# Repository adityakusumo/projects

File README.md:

# FPGA & Embedded Systems Portfolio

Welcome to my portfolio of FPGA and Embedded Systems projects. This repository showcases various hardware designs (KiCad), SoC implementations (LiteX), and firmware development (C/RISC-V) across different FPGA platforms.

## 🚀 Projects Overview

| Project | Platform | Key Features |
| :--- | :--- | :--- |
| **[01. LCD 10.4" Tester](./01_LCD_Tester_Spartan6)** | Spartan-6 (XC6SLX25) | LVDS high-res portrait display tester, Custom Firmware (ISE/LiteX). |
| **[02. STCC1 Record Module](./02_STCC1_Spartan6_Module)** | Spartan-6 (XC6SLX25) | Custom PCB Design (KiCad), LiteX SoC Integration, DDR3 Memory. |
| **[03. Z-Turn Board SoC](./03_ZTurn_XC7Z020_SoC)** | Zynq-7000 (XC7Z020) | LiteX SoC on MYIR Z-Turn, Temperature Sensing, LVDS support. |
| **[04. Wukong Board SoC](./04_Wukong_XC7A100T_SoC)** | Artix-7 (XC7A100T) | LiteX SoC on Qmtech Wukong, HDMI output, RISC-V (SERV/VexRiscv). |

---

## 🛠 Technologies & Tools

- **Languages:** Verilog, Python (Migen/LiteX), C (Embedded), Bash
- **SoC Framework:** [LiteX](https://github.com/enjoy-digital/litex) (Migen-based SoC builder)
- **EDA Tools:** KiCad (PCB), Xilinx ISE 14.7, Xilinx Vivado
- **Hardware Debugging:** openFPGALoader, litex_term, JTAG, Oscilloscope

---

## 📂 Repository Structure

```text
.
├── 01_LCD_Tester_Spartan6/    # LCD portrait display tester project
├── 02_STCC1_Spartan6_Module/  # Custom Record Module (Hardware + Firmware)
├── 03_ZTurn_XC7Z020_SoC/      # LiteX SoC on Zynq-7000 Platform
└── 04_Wukong_XC7A100T_SoC/    # LiteX SoC on Artix-7 Platform
```

Each directory contains its own documentation and build instructions.

---
*Created and maintained by [Aditya Kusumo](https://github.com/adityakusumo)*

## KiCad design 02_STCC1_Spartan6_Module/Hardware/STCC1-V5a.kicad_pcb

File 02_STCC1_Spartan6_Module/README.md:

# STCC1 Spartan-6 Record Module

This project consists of a custom-designed PCB and a LiteX-based SoC for a data recording module using the Xilinx Spartan-6 FPGA.

## 📂 Project Components

- **[Hardware](./Hardware):** KiCad PCB design files for the STCC1-V5a Record Module. Includes schematics, PCB layout, and production files.
- **[Firmware](./Firmware):** LiteX SoC implementations, including DDR3 support and integration with Xilinx ISE.

## 🛠 Features

- **FPGA:** Spartan-6 XC6SLX25-FTG256.
- **Memory:** DDR3 RAM integration via LiteX.
- **Tools:** KiCad for PCB, LiteX for SoC generation, Xilinx ISE for gateware.

---

## 🚀 Quick Start (Firmware)

1. Navigate to `Firmware/stcc1_xc6slx25/`.
2. Run `./build_firmware.sh b` to build the SoC.
3. Run `./build_firmware.sh m` to compile the RISC-V firmware.
4. Load the bitstream using `openFPGALoader`.

For detailed hardware build instructions, refer to the `Hardware` directory.

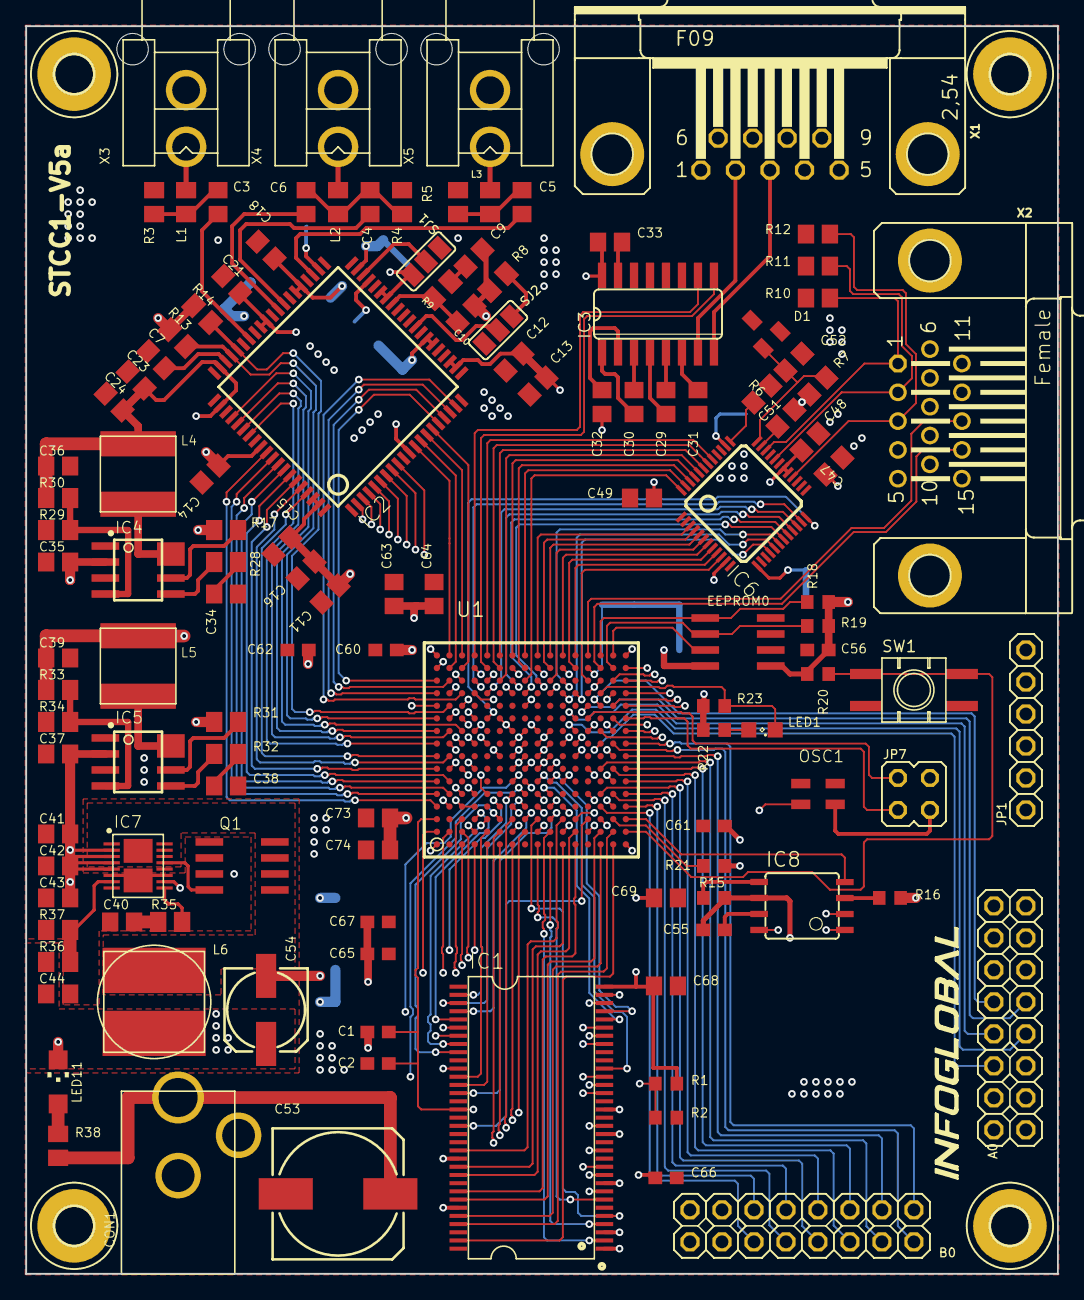
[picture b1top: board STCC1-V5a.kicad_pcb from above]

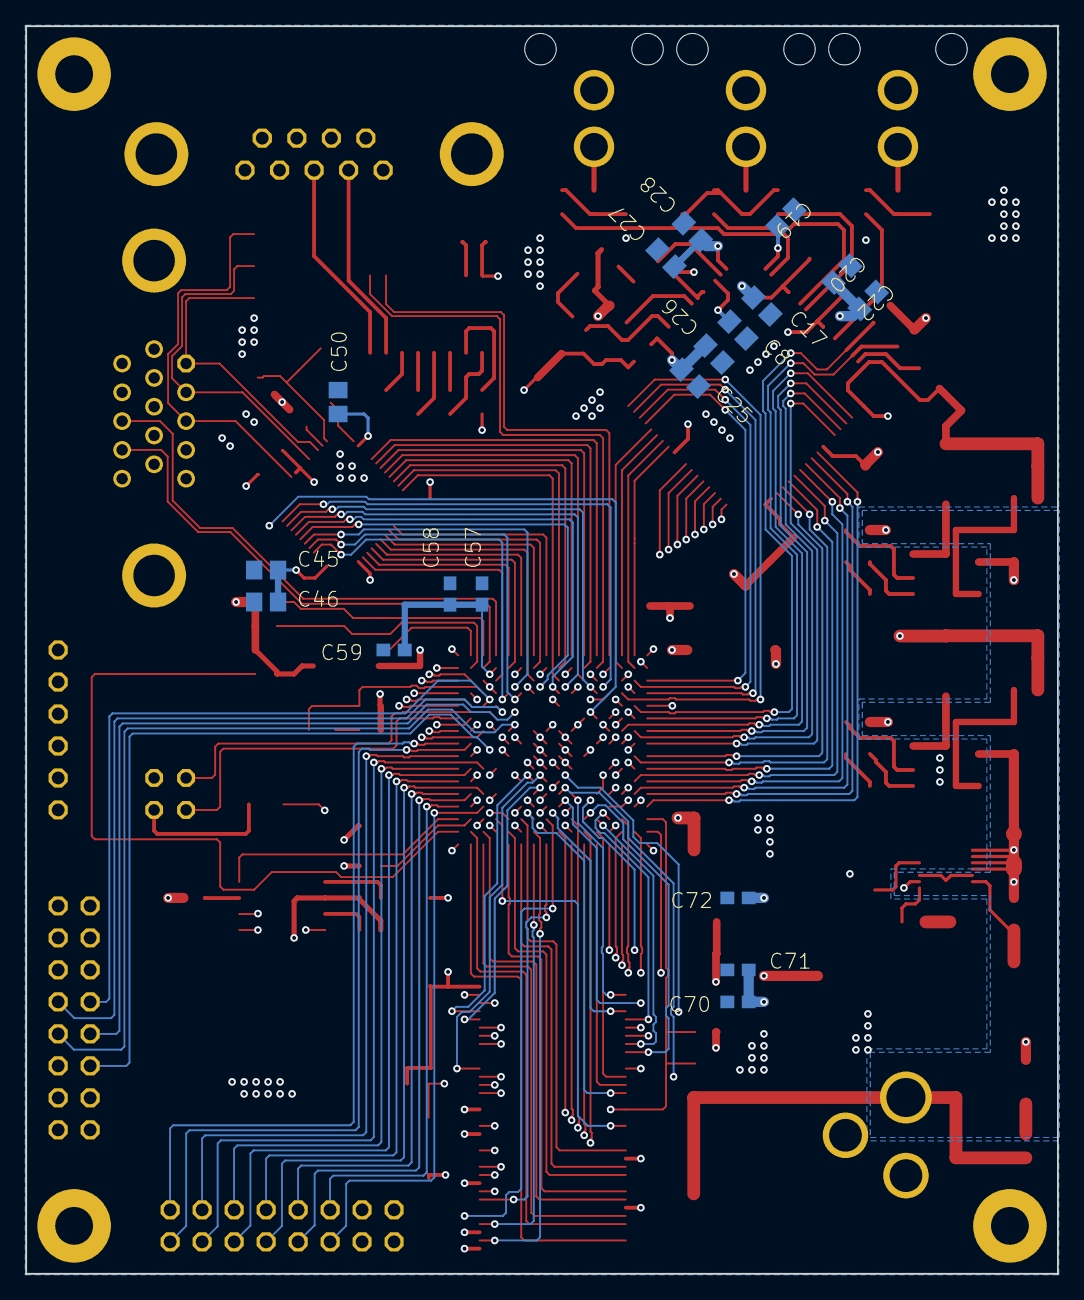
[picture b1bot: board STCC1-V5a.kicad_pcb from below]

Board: 4 copper layers, 81.9 x 99.1 mm, 147 parts (18 on the bottom side), 197 nets.

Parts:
A0: 2X08
B0: 2X08
C1, C2, C57, C58, C59, C60, C61, C62, C65, C66, C67, C70, C71, C72: 4u7; C0603
C3, C4, C5: 47n; C0805
C6: 1n; C0805
C7, C8, C11, C12, C13, C14, C15, C16, C17, C18, C19, C20, C21, C22, C23, C24, C25, C26, C27, C28, C29, C30, C31, C32, C33, C45, C46, C47, C51: 100n; C0805
C9: 82n; C0805
C10: 8.2n; C0805
C34, C38, C40: 2n2; C0805
C35, C37, C41, C42, C43: 10u; C0805
C36, C39, C44, C63, C64, C68, C69, C73, C74: 22u; C0805
C48, C49, C50: 10n; C0805
C52: 1u; C0805
C53: 470u,25V; 153CLV-1014
C54: 100u,16V; 153CLV-0605
C55, C56: 100n; C0603
CON1: DC_SOCKET5870; PWR-5870
D1: AD1580; SOT23
EEPROM0: AT24C512-BN; SOIC8
H1, H2, H3, H4: MOUNT-PAD-ROUND3.0; 3,0-PAD
IC1: DDR_SDRAM-512X16TSOPII-66; TSOPII-66
IC2: AD9883A; LQFP80
IC3: MAX3232ESE; SO16
IC4, IC5: AOZ1021
IC6: ADV7125; LQFP48
IC7: AOZ1025; DFN-16+2TP
IC8: AT45DB161D-SU; 8S2
JP1: 1X06
JP7: JP2Q
L1, L2, L3: FR; M0805
L4, L5: 4.7u; NR60
L6: 1.5u; VLP80
LED1: GRN; SML0805
LED11: RED; CHIPLED_1206
OSC1: 50Mhz; ASE
Q1: SO-08
R1, R2: 220; R0603
R3, R4, R5: 75; M0805
R6: 560; R0805
R7: 1k; R0805
R8: 10k; M0805
R9: 2k7; M0805
R10, R11, R12: 75; R0805
R13, R14: 4k7; M0805
R15, R16, R20, R21: 4k7; R0603
R17, R28, R29, R31, R32: 7k5; M0805
R18, R19: 1k2; R0603
R22: 1k; R0603
R23: 330; R0603
R30, R34, R37: 2k4; M0805
R33: 5k4; M0805
R35: 25k; M0805
R36: 1k2; M0805
R38: 4K7; M0805
SJ1, SJ2: SJ_2
SW1: RESET; PB0_SMD
U1: 6SLX25FTG256; FT256
U$7: LOGO_MEDIUM
X1: F09HP
X2: HDF15H
X3, X4, X5: RCA1X

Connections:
+1.2V: C44.1, C54.+, C70.1, C71.1, C72.1, C73.1, C74.1, L6.P$2, R36.2, U1.G7, U1.G9, U1.H8, U1.H10, U1.J7, U1.J9, U1.K8, U1.K10
+2.5V: C1.1, C39.1, C65.1, C66.1, C67.1, C68.1, C69.1, IC1.1, IC1.3, IC1.9, IC1.15, IC1.18, IC1.33, IC1.55, IC1.61, L5.P$1, R1.2, R33.2, U1.D2, U1.E5, U1.F8, U1.F11, U1.G4, U1.G10, U1.H6, U1.J2, U1.J10, U1.K4, U1.L6, U1.L9, U1.N2
+3V3: A0.3, A0.4, B0.3, B0.4, C9.2, C10.2, C11.1, C12.1, C13.1, C14.1, C15.1, C16.1, C17.1, C18.1, C19.1, C20.1, C21.1, C22.1, C23.1, C24.1, C25.1, C26.1, C27.1, C28.1, C32.2, C33.2, C36.1, C45.1, C46.1, C47.1, C48.1, C49.1, C50.1, C51.2, C55.1, C56.2, C57.1, C58.1, C59.1, C60.1, C61.1, C62.1, C63.1, C64.1, EEPROM0.1, EEPROM0.8, IC2.11, IC2.22, IC2.23, IC2.26, IC2.27, IC2.34, IC2.35, IC2.39, IC2.42, IC2.45, IC2.46, IC2.51, IC2.52, IC2.59, IC2.62, IC2.69, IC2.78, IC2.79, IC3.16, IC6.11, IC6.13, IC6.29, IC6.30, IC6.38, IC8.6, JP1.2, JP7.2, L4.P$1, OSC1.4, R7.2, R8.2, R13.2, R14.2, R15.2, R16.2, R18.2, R19.2, R20.2, R21.2, R22.1, R23.2, R29.2, SJ1.3, U1.B4, U1.B9, U1.B13, U1.D7, U1.D10, U1.D15, U1.G13, U1.J15, U1.K13, U1.N7, U1.N10, U1.N15, U1.R4, U1.R8, U1.R13
A0: IC1.29, U1.K5
A1: IC1.30, U1.K6
A2: IC1.31, U1.D1
A3: IC1.32, U1.L4
A4: IC1.35, U1.G5
A5: IC1.36, U1.H4
A6: IC1.37, U1.H3
A7: IC1.38, U1.D3
A8: IC1.39, U1.B2
A9: IC1.40, U1.A2
A10: IC1.28, U1.G6
A11: IC1.41, U1.E3
A12: IC1.42, U1.F3
AN_BLUE_IN: L3.1, X5.2
AN_GREEN_IN: L2.1, X4.2
AN_RED_IN: L1.1, X3.2
BA0: IC1.26, U1.C3
BA1: IC1.27, U1.C2
BLUE: IC6.28, R12.2, X2.3
BLUE<0>: IC2.19, U1.C13
BLUE<1>: IC2.18, U1.A13
BLUE<2>: IC2.17, U1.B14
BLUE<3>: IC2.16, U1.A14
BLUE<4>: IC2.15, U1.C15
BLUE<5>: IC2.14, U1.C16
BLUE<6>: IC2.13, U1.B15
BLUE<7>: IC2.12, U1.B16
CAS#: IC1.22, U1.H5
CLKE: IC1.44, U1.F4
CLKN: IC1.46, U1.E1
CLKP: IC1.45, U1.E2
CLK_50MHZ: OSC1.3, U1.M9
DATACK_OUT: IC2.67, U1.A9
DONE: LED1.C, R23.1, U1.P13
DQ0: IC1.2, U1.K2
DQ1: IC1.4, U1.K1
DQ2: IC1.5, U1.J3
DQ3: IC1.7, U1.J1
DQ4: IC1.8, U1.F2
DQ5: IC1.10, U1.F1
DQ6: IC1.11, U1.G3
DQ7: IC1.13, U1.G1
DQ8: IC1.54, U1.L3
DQ9: IC1.56, U1.L1
DQ10: IC1.57, U1.M2
DQ11: IC1.59, U1.M1
DQ12: IC1.60, U1.P2
DQ13: IC1.62, U1.P1
DQ14: IC1.63, U1.R2
DQ15: IC1.65, U1.R1
EEPROM_SCL: EEPROM0.6, R19.1, U1.R15
EEPROM_SDA: EEPROM0.5, R18.1, U1.P16
EEPROM_WP: EEPROM0.7, U1.R16
FLASH_MISO: IC8.8, U1.P10
FLASH_MOSI: IC8.1, U1.T10
FLASH_SCK: IC8.2, U1.R11
FLASH_SS: IC8.4, U1.T3
GND: A0.1, A0.2, B0.1, B0.2, C2.2, C7.1, C8.1, C11.2, C12.2, C13.2, C14.2, C15.2, C16.2, C17.2, C18.2, C19.2, C20.2, C21.2, C22.2, C23.2, C24.2, C25.2, C26.2, C27.2, C28.2, C31.1, C33.1, C34.2, C35.2, C36.2, C37.2, C38.2, C39.2, C40.2, C41.2, C42.2, C43.2, C44.2, C45.2, C46.2, C47.2, C48.2, C49.2, C50.2, C52.2, C53.-, C54.-, C55.2, C56.1, C57.2, C58.2, C59.2, C60.2, C61.2, C62.2, C63.2, C64.2, C65.2, C66.2, C67.2, C68.2, C69.2, C70.2, C71.2, C72.2, C73.2, C74.2, CON1.3, D1.2, EEPROM0.2, EEPROM0.3, EEPROM0.4, IC1.6, IC1.12, IC1.24, IC1.34, IC1.48, IC1.52, IC1.58, IC1.64, IC1.66, IC2.1, IC2.10, IC2.20, IC2.21, IC2.24, IC2.25, IC2.28, IC2.32, IC2.36, IC2.40, IC2.41, IC2.44, IC2.47, IC2.50, IC2.53, IC2.55, IC2.60, IC2.61, IC2.63, IC2.68, IC2.80, IC3.15, IC4.AGND, IC4.PGND, IC5.AGND, IC5.PGND, IC6.1, IC6.2, IC6.12, IC6.14, IC6.15, IC6.25, IC6.26, IC6.27, IC6.31, IC6.33, IC6.39, IC6.40, IC7.6, IC7.11, IC7.18, IC8.7, JP1.1, JP7.4, LED11.C, OSC1.2, Q1.1, Q1.2, Q1.3, R2.1, R3.1, R4.1, R5.1, R6.2, R10.1, R11.1, R12.1, R30.1, R34.1, R37.1, SJ1.1, SJ2.1, SW1.1, SW1.2, U1.A1, U1.A16, U1.B7, U1.B11, U1.C4, U1.D4, U1.D13, U1.E9, U1.G2, U1.G8, U1.G15, U1.H7, U1.H9, U1.H12, U1.J5, U1.J8, U1.K7, U1.K9, U1.L2, U1.L15, U1.M8, U1.N13, U1.P3, U1.P14, U1.R6, U1.R10, U1.T1, U1.T16, X1.5, X1.G1, X1.G2, X2.5, X2.6, X2.7, X2.8, X2.10, X2.G1, X2.G2, X3.1, X4.1, X5.1
GREEN: IC6.32, R11.2, X2.2
GREEN<0>: IC2.9, U1.A12
GREEN<1>: IC2.8, U1.D11
GREEN<2>: IC2.7, U1.C11
GREEN<3>: IC2.6, U1.D9
GREEN<4>: IC2.5, U1.C9
GREEN<5>: IC2.4, U1.C7
GREEN<6>: IC2.3, U1.D5
GREEN<7>: IC2.2, U1.C5
HSYNC_OUT: IC2.66, U1.B10
H_SYNC: U1.N16, X2.13
I2C_SCL: IC2.56, R14.1, U1.B12
I2C_SDA: IC2.57, R13.1, U1.A11
INIT_B: R21.1, U1.R3
IO_A5: A0.5, U1.N5
IO_A6: A0.6, U1.P9
IO_A7: A0.7, U1.M10
IO_A8: A0.8, U1.M11
IO_A9: A0.9, U1.N12
IO_A10: A0.10, U1.P12
IO_A11: A0.11, U1.T12
IO_A12: A0.12, U1.R12
IO_A13: A0.13, U1.T13
IO_A14: A0.14, U1.T14
IO_A15: A0.15, U1.R14
IO_A16: A0.16, U1.T15
IO_B5: B0.5, U1.P4
IO_B6: B0.6, U1.T4
IO_B7: B0.7, U1.R5
IO_B8: B0.8, U1.T5
IO_B9: B0.9, U1.P5
IO_B10: B0.10, U1.T6
IO_B11: B0.11, U1.R7
IO_B12: B0.12, U1.T7
IO_B13: B0.13, U1.P7
IO_B14: B0.14, U1.T8
IO_B15: B0.15, U1.R9
IO_B16: B0.16, U1.T9
LDM: IC1.20, U1.J4
LDQS: IC1.16, U1.H2
M0: JP7.1, U1.T11
M1: JP7.3, U1.N11
unnamed: IC8.3, R16.1
unnamed: C3.1, L1.2, R3.2
unnamed: C3.2, IC2.54
unnamed: IC2.38, SJ1.2
unnamed: C4.2, IC2.48
unnamed: C5.1, L3.2, R5.2
unnamed: C5.2, IC2.43
unnamed: IC8.5, R15.1
unnamed: C6.2, IC2.49
unnamed: C4.1, C6.1, L2.2, R4.2
unnamed: C10.1, IC2.33, R9.2
unnamed: R8.1, SJ2.3
unnamed: IC2.29, SJ2.2
unnamed: C7.2, IC2.58
unnamed: C8.2, IC2.37
unnamed: C32.1, IC3.2
unnamed: C9.1, R9.1
unnamed: LED1.A, R22.2
unnamed: IC6.37, R6.1
unnamed: C52.1, D1.1, IC6.36, R7.1
unnamed: C31.2, IC3.6
unnamed: C30.2, IC3.1
unnamed: C29.1, IC3.4
unnamed: C30.1, IC3.3
unnamed: C29.2, IC3.5
unnamed: C51.1, IC6.35
unnamed: IC4.EN, R17.1
unnamed: IC4.LX, L4.P$2
unnamed: IC4.COMP, R28.2
unnamed: C34.1, R28.1
unnamed: IC4.FB, R29.1, R30.2
unnamed: IC5.COMP, R32.2
unnamed: C38.1, R32.1
unnamed: IC5.EN, R31.1
unnamed: IC7.1, IC7.14, IC7.15, IC7.16, IC7.17, L6.P$1, Q1.5, Q1.6, Q1.7, Q1.8
unnamed: IC5.LX, L5.P$2
unnamed: IC7.13, Q1.4
unnamed: IC5.FB, R33.1, R34.2
unnamed: IC7.7, R36.1, R37.2
unnamed: IC7.9, R35.2
unnamed: C40.1, R35.1
unnamed: LED11.A, R38.1
PROG_B: R20.1, SW1.3, SW1.4, U1.T2
RAS#: IC1.23, U1.J6
RED: IC6.34, R10.2, X2.1
RED<0>: IC2.77, U1.A8
RED<1>: IC2.76, U1.B8
RED<2>: IC2.75, U1.A7
RED<3>: IC2.74, U1.B6
RED<4>: IC2.73, U1.A6
RED<5>: IC2.72, U1.B5
RED<6>: IC2.71, U1.A5
RED<7>: IC2.70, U1.A4
RXD: IC3.9, U1.E15
SOG_OUT: IC2.65, U1.A10
TCK: JP1.5, U1.C14
TDI: JP1.4, U1.C12
TDO: JP1.3, U1.E14
TMS: JP1.6, U1.A15
TXD: IC3.10, U1.D16
UART_RX: IC3.8, X1.3
UART_TX: IC3.7, X1.2
UDM: IC1.47, U1.K3
UDQS: IC1.51, U1.N3
VGA_BLU0: IC6.16, U1.M13
VGA_BLU1: IC6.17, U1.L13
VGA_BLU2: IC6.18, U1.L14
VGA_BLU3: IC6.19, U1.J14
VGA_BLU4: IC6.20, U1.H13
VGA_BLU5: IC6.21, U1.G14
VGA_BLU6: IC6.22, U1.E13
VGA_BLU7: IC6.23, U1.D14
VGA_CLOCK: IC6.24, U1.E11
VGA_GRN0: IC6.3, U1.J16
VGA_GRN1: IC6.4, U1.K15
VGA_GRN2: IC6.5, U1.K16
VGA_GRN3: IC6.6, U1.K14
VGA_GRN4: IC6.7, U1.L16
VGA_GRN5: IC6.8, U1.M15
VGA_GRN6: IC6.9, U1.M16
VGA_GRN7: IC6.10, U1.N14
VGA_RED0: IC6.41, U1.E16
VGA_RED1: IC6.42, U1.F15
VGA_RED2: IC6.43, U1.F16
VGA_RED3: IC6.44, U1.F14
VGA_RED4: IC6.45, U1.G16
VGA_RED5: IC6.46, U1.H15
VGA_RED6: IC6.47, U1.H16
VGA_RED7: IC6.48, U1.H14
VIN: C35.1, C37.1, C41.1, C42.1, C43.1, C53.+, CON1.1, IC4.VIN, IC5.VIN, IC7.2, IC7.3, IC7.4, IC7.5, IC7.10, R17.2, R31.2, R38.2
VREF: C1.2, C2.1, IC1.49, R1.1, R2.2, U1.A3, U1.M3
VSYNC_OUT: IC2.64, U1.C10
V_SYNC: U1.P15, X2.14
WE#: IC1.21, U1.C1
